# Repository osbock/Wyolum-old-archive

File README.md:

# Wyolum-old-archive aka the google code clockthree repo
This is an archive of the old Wyolum Google code repo.
New commits should not be made here.
See instead separate repositories under:
http://github.com/wyolum

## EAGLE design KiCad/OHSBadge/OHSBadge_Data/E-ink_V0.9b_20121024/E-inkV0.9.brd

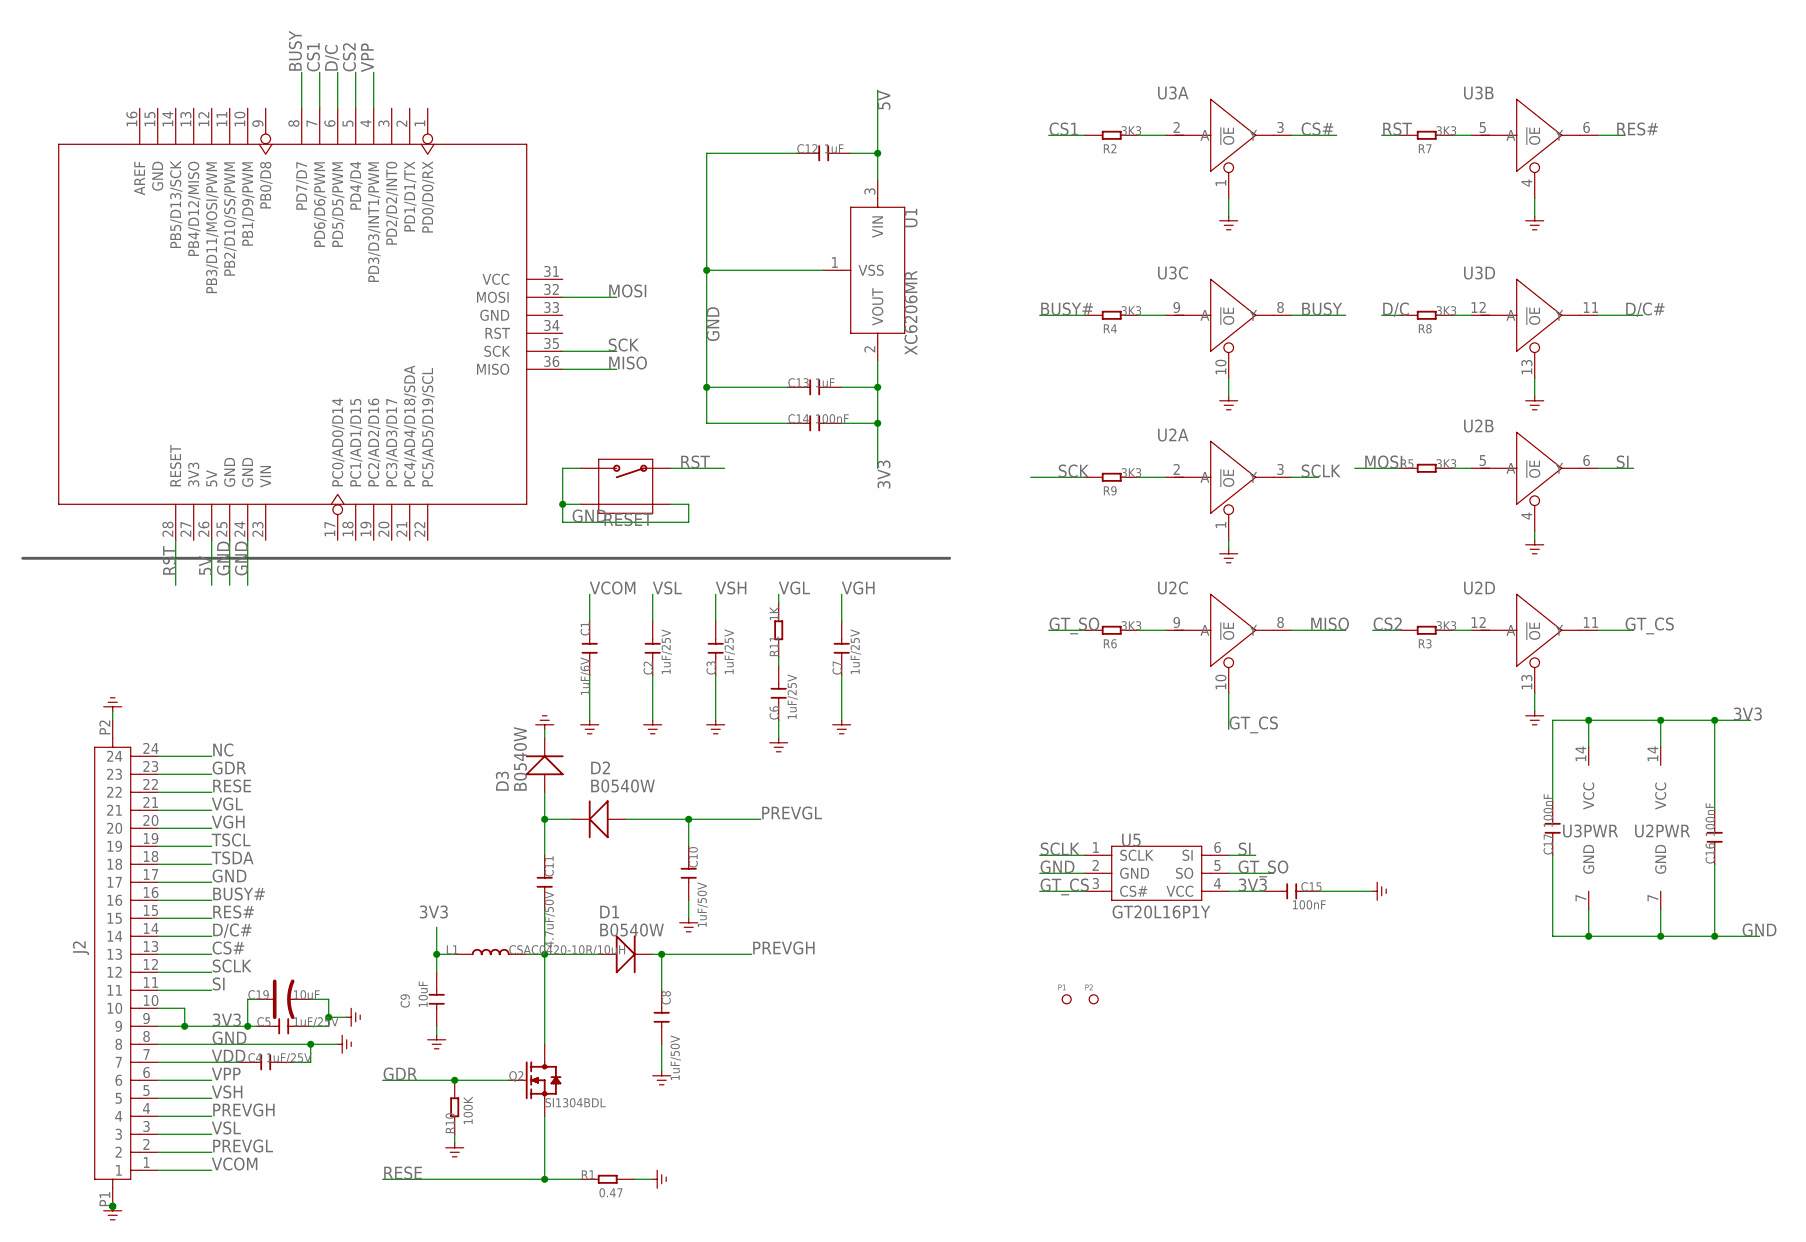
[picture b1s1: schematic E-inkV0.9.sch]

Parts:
C1: 1uF/6V; C0805
C2, C3, C4, C5, C6, C7: 1uF/25V; C0805
C8, C10: 1uF/50V; C0805
C9: 10uF; C0805
C11: 4.7uF/50V; C0805
C12, C13: 1uF; C0805
C14, C15, C16, C17: 100nF; C0603
C19: 10uF; AVX-A
D1, D2, D3: B0540W; SOD123-2.7X1.6
J2: FPC_CONNECTOR; 24P-0.5
L1: CSAC0420-10R/10uH; 1616BZ
P1, P2: PAD-MARK; ROUND-MARK-1.0
Q2: SI1304BDL; SOT323
R1: 0.47; R0603
R2, R3, R4, R5, R6, R7, R8, R9: 3K3; R0603
R10: 100K; R0603
R11: 1K; R0603
RESET: FOR_TEST_ALBERT_V6_BUTTON_4P_SMD; FOR_TEST_ALBERT_V6_4P-SMD-7X3.5X3.5
U1: XC6206MR; SOT23
U2, U3: 74VHC125PW; TSSOP14
U4: ARDUINO; ARDUINO-ISP-SMD
U5: GT20L16P1Y; SOT23-6

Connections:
3V3: C5.1, C9.1, C13.2, C14.2, C15.1, C16.2, C17.2, C19.+, J2.9, J2.10, L1.1, U1.2 (VOUT), U2.14 (VCC), U3.14 (VCC), U5.4 (VCC)
5V: C12.2, U1.3 (VIN), U4.26 (5V)
BUSY: U3.8 (Y), U4.8 (PD7/D7)
BUSY#: J2.16, R4.1
CS1: R2.1, U4.7 (PD6/D6/PWM)
CS2: R3.1, U4.5 (PD4/D4)
CS#: J2.13, U3.3 (Y)
D/C: R8.1, U4.6 (PD5/D5/PWM)
D/C#: J2.14, U3.11 (Y)
GDR: J2.23, Q2.1 (G), R10.2
GND: C1.2, C2.1, C3.1, C4.2, C5.2, C6.1, C7.1, C8.2, C9.2, C10.2, C12.1, C13.1, C14.1, C15.2, C16.1, C17.1, C19.-, D3.2 (-), J2.8, J2.17, J2.P1, J2.P2, R1.2, R10.1, RESET.2, RESET.S1, RESET.S2, U1.1 (VSS), U2.1 (!OE), U2.4 (!OE), U2.7 (GND), U2.13 (!OE), U3.1 (!OE), U3.4 (!OE), U3.7 (GND), U3.10 (!OE), U3.13 (!OE), U4.24 (GND), U4.25 (GND), U5.2 (GND)
GT_CS: U2.10 (!OE), U2.11 (Y), U5.3 (CS#)
GT_SO: R6.1, U5.5 (SO)
MISO: U2.8 (Y), U4.36 (MISO)
MOSI: R5.1, U4.32 (MOSI)
unnamed: C11.1, D2.2 (-), D3.1 (+)
unnamed: C11.2, D1.1 (+), L1.2, Q2.3 (D)
unnamed: R6.2, U2.9 (A)
unnamed: R9.2, U2.2 (A)
unnamed: R4.2, U3.9 (A)
unnamed: R2.2, U3.2 (A)
unnamed: R7.2, U3.5 (A)
unnamed: R3.2, U2.12 (A)
unnamed: R5.2, U2.5 (A)
unnamed: R8.2, U3.12 (A)
unnamed: C6.2, R11.1
NC: J2.24
PREVGH: C8.1, D1.2 (-), J2.4
PREVGL: C10.1, D2.1 (+), J2.2
RES#: J2.15, U3.6 (Y)
RESE: J2.22, Q2.2 (S), R1.1
RST: R7.1, RESET.1, U4.28 (RESET)
SCK: R9.1, U4.35 (SCK)
SCLK: J2.12, U2.3 (Y), U5.1 (SCLK)
SI: J2.11, U2.6 (Y), U5.6 (SI)
TSCL: J2.19
TSDA: J2.18
VCOM: C1.1, J2.1
VDD: C4.1, J2.7
VGH: C7.2, J2.20
VGL: J2.21, R11.2
VPP: J2.6, U4.4 (PD3/D3/INT1/PWM)
VSH: C3.2, J2.5
VSL: C2.2, J2.3

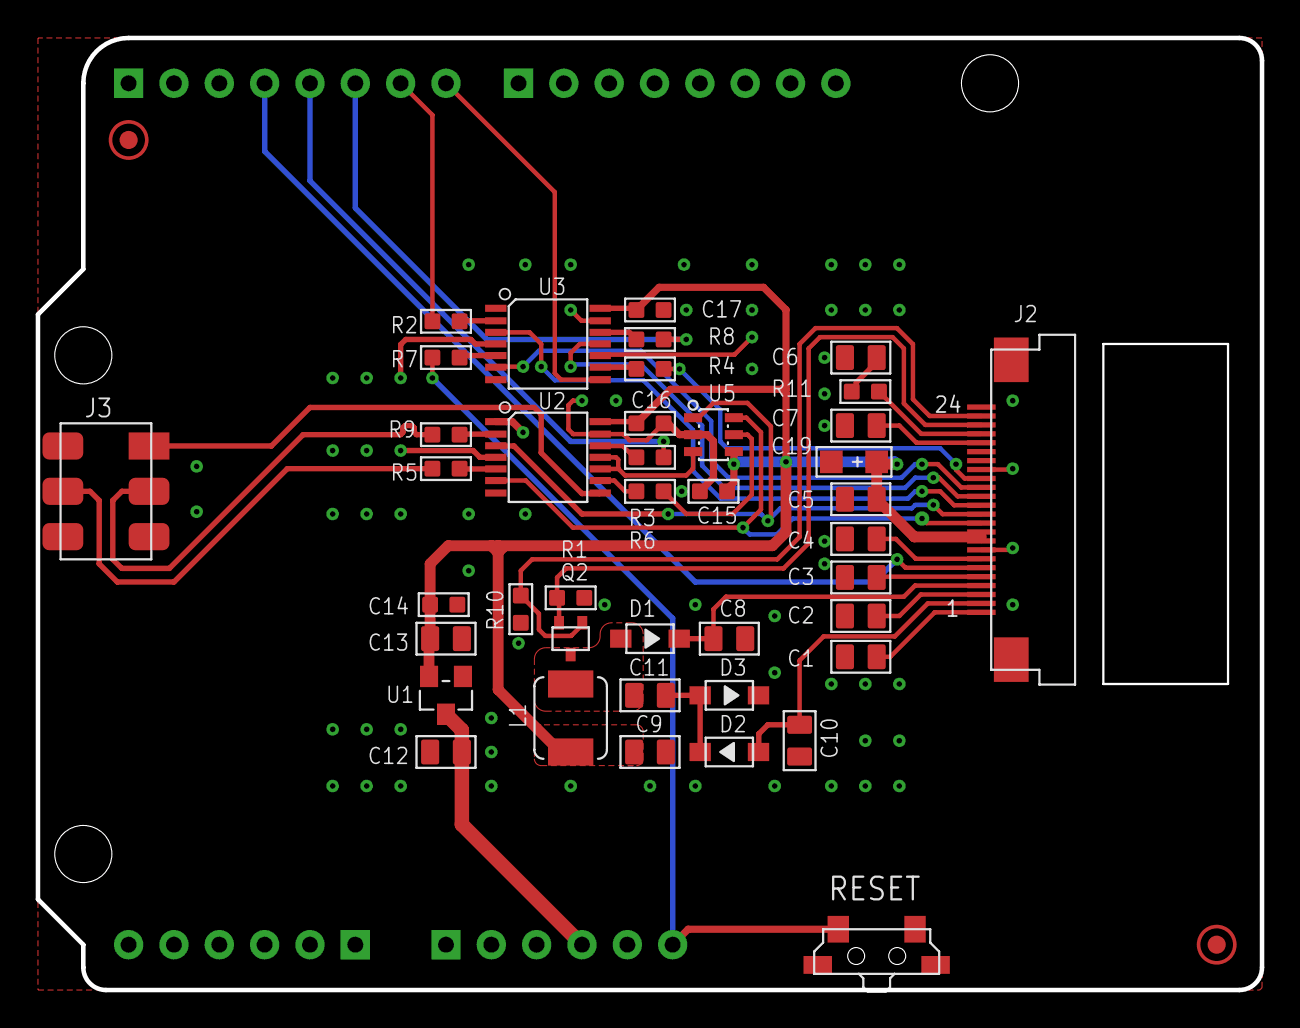
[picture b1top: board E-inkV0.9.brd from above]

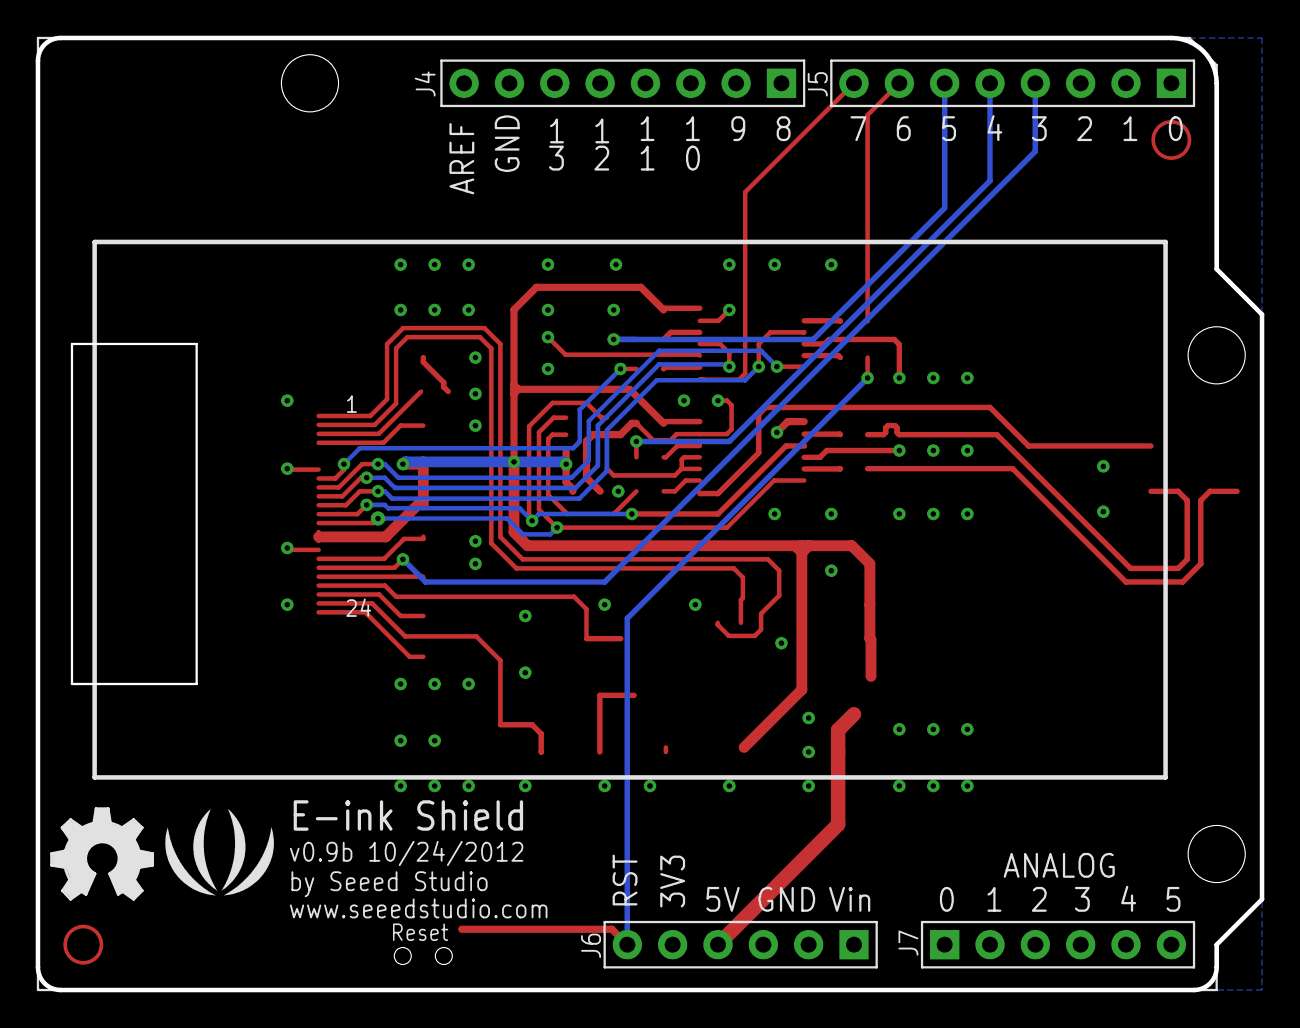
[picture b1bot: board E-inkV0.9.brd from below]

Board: 2 copper layers, 68.6 x 53.3 mm, 45 parts (3 on the bottom side), 41 nets.

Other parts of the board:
U$25: LOGO_SILK
U$26: OSHW_FILLX200_NOTEXT

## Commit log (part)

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2012-06-21 pulse - final gerber files created. BoM finalized
2012-06-22 aLaMode - working on adding in FTDI USB functionality.
2012-06-23 pulse - software done. check in pulse_fader folder.
2012-06-25 pulse - SW mod.
2012-06-25 aLaMode - complete. Final Gerbers and BoM.
2012-06-30 pulse - minor digikey BoM update
2012-07-12 aLaMode - v2, added +5V0, +3V3 and GND headers for Analog Inputs
2012-07-12 BatMon - v2, revised board layout, moved some components around
2012-07-20 fixed double updating
2012-07-21 Name in Lights - NiL - minor library mods
2012-07-21 Added script to set time to whatever for glamour shots. Also does mirror image.
2012-07-23 undefined ATMEGA for production
2012-07-25 p.u.l.s.e - minor changes to the code to make it pulse better. Also, ND pin is set low by default.
2012-07-27 p.u.l.s.e. - updated the sketch
2012-07-28 aLaMode_v2 done. Gerbers generated. But need a final look-over before we send to seeed.
2012-08-07 Change P1 header to female, 4Uconnector example .05" jumper shunts for power, u6 enable RPI interface
2012-08-14 Added I2GPS sketches, Updated TimeZ
2012-08-18 I2GPS codes
2012-08-22 Carduino added few Images. Added sketch Folder
2012-08-23 removed some jumpers
2012-09-05 I2GPS Client test script added.
2012-09-08 I've put in an experimental diming. Problem is that it does not work with fading (when time changes).
    Feel free to test it out. Add the line
    #define DIM
    to ClockTHREE_04. Inc and Dec increase and decrease brightness.
2012-10-15 BPC Pump connector board
2012-10-19 BPC minor silk screen mod.
2012-11-20 i2gps_v1 added Datasheet pdf and images
2012-11-23 C3Jr_v2 added new BoM for retail clock (full assembly at seeed) and files needed for Laser parts
2012-11-23 AlaMode minor mods.
2012-11-25 Added Spec Sheets
2012-11-27 uControl - added schematic page for Interfaces
2012-11-28 uControl schematic development. To Do decide on control pins for Pump, Pressure and Valve
2012-11-30 uControl schematic in progress
2012-11-30 Nb_LED - not final, some clean up pending
2012-12-01 Nb_adapter - added a small adapter for converting 5x2 header to 10x2
2012-12-03 uControl added schematic PDF and some data sheets
2012-12-07 uControl some minor edits to schematic
2012-12-17 uControl added some pdf datasheets
2012-12-20 uControl Footprints work in progress
2012-12-22 uControl Footprints in progress
2012-12-23 uControl Justin, check the Footprints - print the uControl.brd file
2012-12-23 uControl minor mods to footprints
2012-12-25 uControl footprints done. working on initial board layout
2012-12-26 uControl - minor mods to .brd and .mod files.
2012-12-27 uControl footprint layout almost done.
2012-12-28 uControl changed to Thru Hole design. Basic parts laid out. No tracks yet.
2012-12-29 uControl track layout complete. Needs to be checked.
2012-12-30 uControl - board layout done. Needs a good check now.
2012-12-31 uControl track layout done. need to clean up silk legend.
2013-01-01 uControl - Board seems done. Needs some final checks before sending for prototype
2013-01-02 uControl : looks done. Final reviews and checks left. Gerbers ready.
2013-01-03 uControl v1 Prototype complete. Gerbers generated, BoM finalized.
2013-01-04 uControl correction ATMega8 to ATMega328P. changed sch, pcb and BoM files. Also, simplified Manifold design.
2013-01-05 C3Jr_v2_nil couple of images added
2013-01-05 RowGB complete. Need to check PCB layout
2013-01-07 uControl - minor mod to footprint library
2013-01-07 RowGB - modified footprints library to correct path to 3d files.
2013-01-11 KiCad folder, some clean up.
2013-01-16 uControl : Manifold modified - deeper hole for 1/4"-28 UNF Barb taps
2013-01-24 added Xavitech pump documentation.
2013-01-25 uControl : flipped pump connector, added Capacitor for Pump, etc. Also added 3D model of Flow Meter
2013-01-29 Nb_v03 BoM revised.
2013-02-04 Nb_v3 : v3 final Gerbers.
2013-02-05 uControl : added additional footprint for flowmeter. Added 5V regulator for Ras-Pi.
2013-02-07 uControl : some board changes, and added folder for uControl box/case
2013-02-08 uControl 5V breakout board for supply to Ras-Pi from 12V barrel socket.
2013-02-09 uControl : Acrylic box design on single page
2013-02-09 added unit tests for uControl
2013-02-11 TiM layout seems done. Board cleanup required.
2013-02-13 TiM : Need to add legend for stacking connectors.
2013-02-14 TiM : Booya !! Final checks required before prototype boards.
2013-02-15 TiM minor legend clean up
2013-02-18 RowGB and TIM : Final Gerbers generated. Ready for prototype run.
2013-02-18 RasPi_RTC : started new project folder.
2013-02-21 RowGB - updated the Attiny slave controller schematic sheet
2013-02-22 RasPi_RTC : Booya ! to be checked.
2013-02-23 RasPi_RTC : renamed EPOCH. created final Gerber files (some mods in Legend, tracks etc). Created seeed format BOM. Added Logos to Legend.
2013-03-04 uControl : Modified Acrylic box/case files
2013-03-06 smartRGB : x16 row of WS2811 LED Pixels with ATTiny85 controller
2013-03-08 Nachbau_v03 modified BOM Files.
2013-03-10 Nachbau_v03 modified Silk Legend to identify v03
2013-03-12 Changed name of folder (RasPi_RTC to RasPi_Epoch)
2013-03-14 OHSBadge (repaper) converted EPD reference schematic to KiCad format (needs a lot of work, though).
2013-03-15 RasPi_EPOCH : added two projects - Epoch_smd for DS3231 SMD board, and Epoch_TH for DS1307 TH board.
2013-03-15 RasPi_Epoch : Epoch_TH done. Need to verify the circuit and layout.
2013-03-21 Raspi_EPOCH - boards renamed as EPOCH_smd and EPOCH_th. Final gerber plots and BoM files ready.
2013-03-22 EPaper Badge - added seeed reference circuit.
2013-03-23 reverted to original strandtest from github (with minor mod)
2013-03-24 work in progress, cleaning up repaper reference schematic
2013-03-27 repaper badge - schematic work in progress
2013-03-28 new smartRGB folder. Moved files from old OHSBadge to here.
2013-03-29 OHSBadge - Controller to EPD pin connections assigned. Need to check 5V out from Digital Port 10
2013-03-30 OHSBadge - started basic PCB layout
2013-03-31 OHSBadge - smoe edits to footprint libs
2013-04-01 OHSBadge - original design renamed as repaper_dumb. creating a new Schematic with ATMega included.
2013-04-02 OHSBadge : added 328P, and full Arduino shield. See Board outline for lanyard looping option.
2013-04-04 OHSBadge working on board layout.
2013-04-06 Kevin's smartRGB library using Adafruit NeoPixel
2013-04-07 OHSBadge, Schematic update, added coin batt, JST connector, 3V3 selector.
2013-04-08 OHSBadge - getting some basic track layout done
2013-04-09 OHSBadge - track layout done. Added thru hole switches. All SMD parts are on solder side now.
2013-04-09 OHSBadge Switches were reversed (corrected). Added 4th switch (Mode). SPI header pads were mirrored when footprint was flipped over. Moved Voltage SEL P6 to make space for 4th switch.
2013-04-11 OHSBadge : track layout complete. Power section revamped - please check. Some parts need new footprints - Resonator (instead of crystal).
2013-04-12 OHSBadge : added logos. added 12V barrel socket. changed Xtal and Xtal Capacitors footprint. Part2 - internet is acting crappy today.
2013-04-12 OHSBadge : added logos. added 12V barrel socket. changed Xtal and Xtal Capacitors footprint. Part4 - internet is acting crappy today.
2013-04-12 OHSBadge - geberated gerbers to check/verify on OHSPark.com
2013-04-13 OHSBadge-Part2 : Completed. Initial gerbers made for verification. Final checks pending. Added more 3D parts.
2013-04-13 OHSBadge-Part4 : Completed. Initial gerbers made for verification. Final checks pending. Added more 3D parts.
2013-04-13 OHSBadge-Part6 : Completed. Initial gerbers made for verification. Final checks pending. Added more 3D parts.
2013-04-14 OHSBadge : working on the silk legends. Everything else seems almost done.
2013-04-15 OHSBadge : Completed. Gerbers ready for prototyping.
2013-04-15 OHSBadge : a minor clean up of silk legends.
2013-04-16 OHSBadge : checking the layout one final time. Some minor mods made.
2013-04-17 OHSBadge : Final for prototyping.
2013-04-17 OHSBadge : Added file with 3D call outs for OHSBadge. BoM update for 2450 battery/holder. 2450 to 2032 adapter.
2013-04-21 rtcBoB : v2 all SMD. BoM is pending.
2013-04-22 OHSBadge : Corrected Battery Retainer P/N in BoM
2013-04-23 C3v2 : minor mod to BoM file
2013-05-13 OHSBadge : swapped Tx and Rx signals based on seeed feedback.
2013-05-18 added Screen example for TiM
2013-05-24 OHSBadge : created separate folder. Put HW interrupts INT0 and INT1 on switches. Moved uSD card to edge etc. OHS logo with LED heartbeat
2013-05-24 OHSBadge : created separate folder. Put HW interrupts INT0 and INT1 on switches. Moved uSD card to edge etc. OHS logo with LED heartbeat. Part 3
2013-05-31 OHSBadge : Coin Batt slot made wider. Increased [-] pad mask.
2013-06-02 pre disk crash commit
2013-06-03 OHSBadge : v3 Final Prototype. Added PDF Files.
2013-06-05 OHSBadge : BADGEr_v3 Final Prototype. Added PDF Files. Minor mods.
2013-06-07 OHSBadge : BADGEr_v3 Final Prototype. push buttons changed to SMD. Added SMD ON switch for BATTERY. Centered P-Buttons with EPD.
2013-06-07 OHSBadge : BADGEr_v3 Final Prototype. Added Slide Switch 3D Module
2013-06-11 OHSBadge : BADGEr_v4. Disconnect V_IN between Shield and Badge
2013-06-13 OHSBadge : BADGEr_v4. Added DNP to unpopulated parts on schematic. Max. Page turns BATT warning on Back Legend. Breakout Pads for unused Shield headers
2013-06-14 AlaMode_v3 : Updated BOM. Added resistors for GPS Rx.
2013-06-14 AlaMode_v3 : minor clean up, nothing new here.
2013-06-14 BADGEr - added MOSFET data sheet
2013-06-18 AlaMode_v3 : BoM updated - added Bumpon feet.
2013-07-08 uControl : added Zephyr datasheet
2013-07-08 uControl_v2 : renamed the schematic file
2013-07-15 OHSBadge : BADGEr_v4. ICSP Pin 1 legend error corrected. Fresh Gerbers/PDF's generated
2013-07-17 OHSBadge : BADGEr_v4. 2450 Batt Page turns reduced to 100. Fresh Gerbers/PDF's generated
2013-08-13 uControl_v2 : schematic work in progress
2013-08-14 added scad files for manifold
2013-08-14 uControl_v2 schematic progression
2013-08-15 uControl_v2 : added the schematic PDF
2013-08-16 removed rouned corners
2013-08-17 added manifold to uControl_v2 directory
2013-08-17 uControl_v2 progress : Pump 3d added
2013-08-18 uControl_v2 : 3D modules for Flow, Pump, Valve, Pr sensors
2013-08-21 uControl_v2 - laying out the parts on the board
2013-08-22 uControl_v2 : Farm enclosure files added.
2013-08-23 uControl_v2 : minor mods
2013-08-24 uControl_v2 : working on getting PiPower 3D in to the board to allow proper placement.
2013-08-25 uControl_v2 : Moved parts around - Pr Gauge, RasPi etc
2013-08-26 uControl_v2 : Ready to stary layout once RasPi and Gage orientation is finalized
2013-09-01 uControl_v2 : working on track layout. half way through.
2013-09-11 uControl_v2 : track layout in progress. 3 tracks left to go.
2013-09-19 uControl_v2 : track layout complete. Silk Legend in progress
2013-09-23 OHSBadge : BADGEr_v4. Dimensional drawings created - pdf and dxf
2013-09-26 uControl_v2 working on modifying new pump
2013-09-28 uControl_v2 : Copper fill zones, Legend done. Moved LED's so they are visible (were located under PiPower earlier), and other mods.
2013-09-28 added connector data sheet
2013-09-30 uControl_v2 : Modified PiPower outline (56mm wide)
2013-12-02 added some data sheets
2013-12-05 uControl_v3 created new folder for uControl using BBB instead of Ras-Pi (_v2) #1 Base files
2013-12-05 uControl_v3 created new folder for uControl using BBB instead of Ras-Pi (_v2) #3 3D Modules
2013-12-07 uControl_v2 added pdf files for PCB
2013-12-07 uControl_v3 added BBB 3D module
2013-12-11 AlaMode_v3 added Board dimensions
2013-12-16 Defined keep out zone
2013-12-21 uControl_v3 work in progress
2013-12-29 uCv3 added 5V<>3V discrete converter with break out pads. Final checks to be done
2013-12-31 uCv3 working on the BoM
2014-02-19 aLaMode_v3 added 3D files
2014-07-21 added an images
2016-03-06 Migrating wiki contents from Google Code
